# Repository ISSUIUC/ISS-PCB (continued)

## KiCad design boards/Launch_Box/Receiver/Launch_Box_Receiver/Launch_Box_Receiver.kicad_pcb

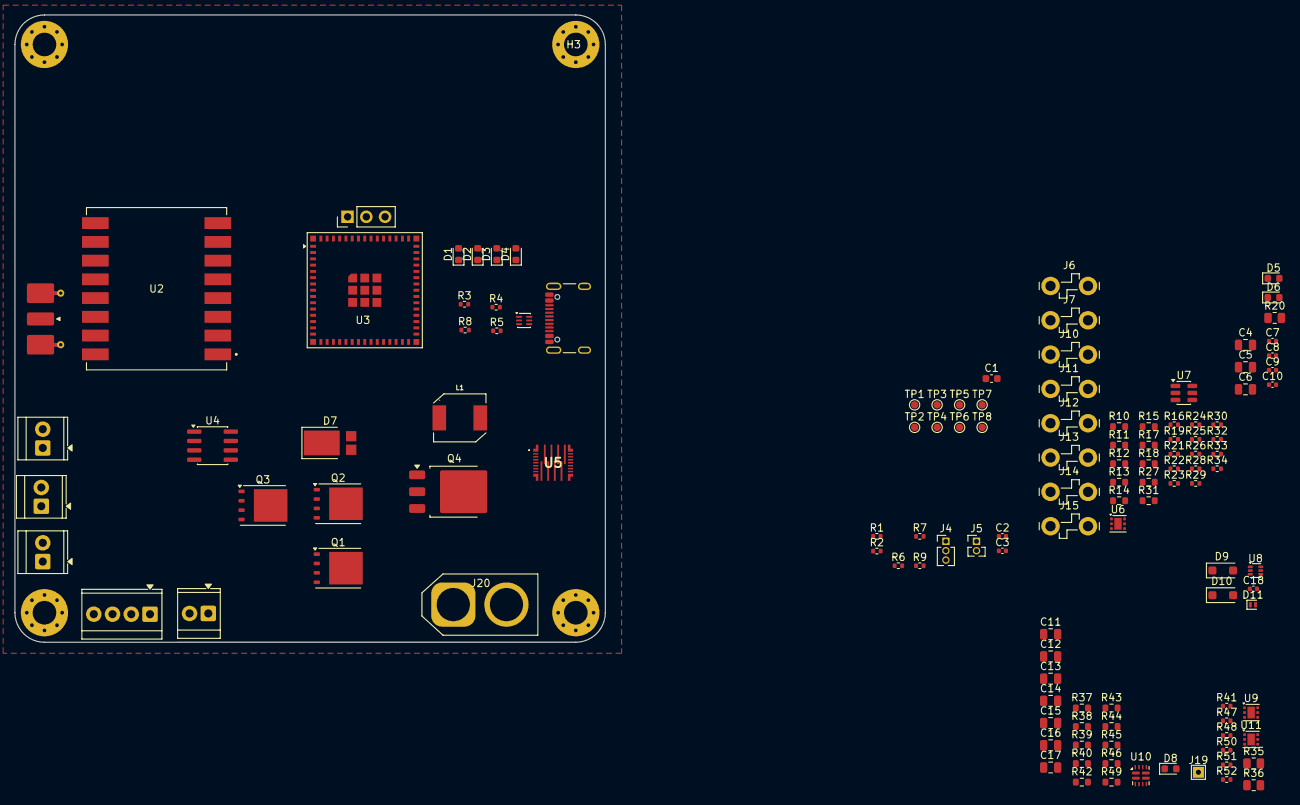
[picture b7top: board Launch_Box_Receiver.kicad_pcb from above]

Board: 4 copper layers, 80.0 x 85.0 mm, 129 parts (0 on the bottom side), 81 nets, no tracks yet.

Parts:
C1: 22uF; C_0603_1608Metric
C2: 100nF; C_0402_1005Metric
C3, C18: 1uF; C_0402_1005Metric
C4, C5: 4.7uF; C_0805_2012Metric
C6: 2.2uF; C_0805_2012Metric
C7, C8: 22pF; C_0402_1005Metric
C9: 1nF; C_0402_1005Metric
C10: 22nF; C_0402_1005Metric
C11: 0.1uF; C_0805_2012Metric
C12, C13: 10uF; C_0805_2012Metric
C14, C15, C16, C17: 22uF; C_0805_2012Metric
D1, D8: RED LED; LED_0603_1608Metric
D2: ORANGE LED; LED_0603_1608Metric
D3: GREEN LED; LED_0603_1608Metric
D4: BLUE LED; LED_0603_1608Metric
D5, D6: BLUE_LED; LED_0603_1608Metric
D7: SBR10U45SP5; D_PowerDI-5
D9: BZT52H-A5V1-QX; D_SOD-123F
D10: BZT52H-C15; D_SOD-123F
D11: BAS116L; D_SOD-882
H1, H2, H3, H4: M3; MountingHole_3.2mm_M3_Pad_Via
J1: USB4105-GF-A; USB_C_Receptacle_GCT_USB4105-xx-A_16P_TopMnt_Horizontal
J2: SMA; SMA_Molex_73251-2120_EdgeMount_Horizontal
J3: Conn_01x03; PinHeader_1x03_P2.54mm_Vertical
J4: Conn_01x03; PinHeader_1x03_P1.27mm_Vertical
J5: Conn_01x02; PinHeader_1x02_P1.27mm_Vertical
J6, J7, J10, J11, J12, J13, J14, J15: TE_1217861-1; TE_1217861-1_Faston_6.35mm_Vertical
J8: Screw_Terminal_01x04; TerminalBlock_TE_282834-4_1x04_P2.54mm_Horizontal
J9, J16, J17, J18: Screw_Terminal_01x02; TerminalBlock_TE_282834-2_1x02_P2.54mm_Horizontal
J19: TestPoint; TestPoint_THTPad_1.5x1.5mm_Drill0.7mm
J20: XT60 Male; AMASS_XT60-M_1x02_P7.20mm_Vertical
L1: 2.2uH; L_TDK_SPM6530
Q1, Q2, Q3: CSD17312Q5; TDSON-8-1
Q4: IPD068P03L3; TO-252-3_TabPin2
R1, R2: 5.1k; R_0402_1005Metric
R3, R4, R5, R8, R21, R22, R41: 470; R_0402_1005Metric
R6, R7: 4.7k; R_0402_1005Metric
R9: 20k; R_0402_1005Metric
R10, R11, R27, R38, R42: 200k; R_0603_1608Metric
R12, R14: 549; R_0603_1608Metric
R13, R15, R31, R46: 22k; R_0603_1608Metric
R16: 549; R_0402_1005Metric
R17, R18: 3.3k; R_0603_1608Metric
R19: 3.3k; R_0402_1005Metric
R20: 0R; R_0805_2012Metric
R23, R32: 100k; R_0402_1005Metric
R24, R25, R26: 10k; R_0402_1005Metric
R28: 10R; R_0402_1005Metric
R29, R30: 270R; R_0402_1005Metric
R33: 1.54k; R_0402_1005Metric
R34: 3.65k; R_0402_1005Metric
R35, R36: 2k; R_0805_2012Metric
R37: 470; R_0603_1608Metric
R39: 20k; R_0603_1608Metric
R40: 135k; R_0603_1608Metric
R43, R44: 30k; R_0603_1608Metric
R45: 26.1k; R_0603_1608Metric
R47: 62k; R_0402_1005Metric
R48: 16.9k; R_0402_1005Metric
R49: 100k; R_0603_1608Metric
R50: 21.5k; R_0402_1005Metric
R51, R52: 4.99k; R_0402_1005Metric
TP1, TP2, TP3, TP4, TP5, TP6, TP7, TP8: TestPoint_Small; TestPoint_Pad_D1.0mm
U1: ECMF02-2AMX6; ST_UQFN-6L_1.5x1.7mm_P0.5mm
U2: CORE1262-868M; XCVR_CORE1262-868M
U3: ESP32-S3-MINI-1U-N8; ESP32-S2-MINI-1U
U4: LM293; SOIC-8_3.9x4.9mm_P1.27mm
U5: TPS25990ARQPR; VQFN26_RQP_TEX
U6, U9, U11: TVS1400DRV; WSON-6-1EP_2x2mm_P0.65mm_EP1x1.6mm
U7: SRV05-4; SOT-23-6
U8: TI_TPS566242; SOT-563
U10: TPS2121; Texas_VQFN-HR-12_2x2.5mm_P0.5mm

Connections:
12V_VBAT: C5.1, D10.1 (K), Q4.3 (S), R20.1, R28.1, R47.1, U5.23 (VIN), U5.24 (VIN), U5.25 (VIN), U5.26 (VIN), U9.4 (IN), U9.5 (IN), U9.6 (IN), U10.7 (IN1)
+3V3: C1.1, C2.1, C14.1, C15.1, C16.1, C17.1, L1.1, R6.2, R7.2, R9.2, R23.1, R24.1, R25.1, R26.1, R37.1, R38.1, R40.2, R41.1, U2.8 (3V3), U3.3 (3V3), U4.8 (V+), U7.5 (VP)
/ALARM: R16.1, R19.1, U3.14 (IO10)
/ANT_SX1262: J2.1 (In), U2.16 (ANT)
/BOOT_SW: J3.1, U3.4 (IO0), U7.6 (IO4)
/CONTINUITY_1_LED: R21.1, R29.1, U3.12 (IO8), U7.1 (IO1)
/CONTINUITY_2_LED: R22.1, R30.1, U3.13 (IO9), U7.3 (IO2)
/D+: J1.A6 (D+), J1.B6 (D+), U1.6 (D+_out)
/D-: J1.A7 (D-), J1.B7 (D-), U1.5 (D-_out)
/FIRE_1: R12.2, R17.1, TP8.1 (1_1), U3.15 (IO11)
/FIRE_2: R14.2, R18.1, TP7.1 (1_1), U3.16 (IO12)
/I2C_SCL: J5.2, R7.1, U3.37 (IO41), U5.16 (SCL)
/I2C_SDA: J5.1, R6.1, U3.36 (IO40), U5.15 (SDA)
/IGN1_SENSE: R10.1, R13.1, U3.5 (IO1)
/IGN2_SENSE: R11.1, R15.1, U3.6 (IO2)
/LED_BLUE: R8.1, U3.19 (IO15)
/LED_GREEN: R5.1, U3.20 (IO16)
/LED_ORANGE: R4.1, U3.21 (IO17)
/LED_RED: R3.1, U3.22 (IO18)
/NFAULT: R26.2, U3.27 (IO47), U5.20 (GPIO2/FLT/COMP1/COMP2/EEDATA/EECLK)
/PG: R25.2, U3.25 (IO21), U5.19 (GPIO1/PGOOD/COMP1/COMP2/EEDATA/EECLK)
/Power/PMUX_GND: C18.1, D11.2 (A), R50.1, R51.2, R52.2, U10.3 (CP2), U10.6 (PR1), U10.9 (ST), U10.12 (GND)
/Power/VSYS: C11.1, C12.1, C13.1, J19.1 (Pin_1_1), R35.1, R39.1, R42.1, U8.1 (VIN), U10.1 (OUT), U10.8 (OUT)
/RESET_SW: C3.1, J3.2, R9.1, U3.45 (EN), U7.4 (IO3)
/SMBUS_ALERT: R24.2, U3.38 (IO42), U5.17 (GPIO4/SMBA/COMP1/COMP2/EEDATA/EECLK)
/SPI0_MISO: J4.3, U2.11 (MISO), U3.29 (IO34)
/SPI0_MOSI: J4.2, U2.12 (MOSI), U3.31 (IO35)
/SPI0_SCK: J4.1, U2.13 (CLK), U3.32 (IO36)
/SX1262_BUSY: U2.9 (BUSY), U3.26 (IO26)
/SX1262_CS: TP4.1 (1_1), U2.14 (CS), U3.40 (RXD0)
/SX1262_GPIO_1: U2.6 (DIO1), U3.18 (IO14)
/SX1262_GPIO_2: U2.5 (DIO2), U3.17 (IO13)
/SX1262_RESET: U2.10 (RESET), U3.28 (IO33)
/SX1262_RX_EN: TP6.1 (1_1), U2.3 (RXEN), U3.34 (IO38)
/SX1262_TX_EN: TP5.1 (1_1), U2.4 (TXEN), U3.33 (IO37)
/USB_D+: U1.1 (D+_in), U3.24 (USB_D+)
/USB_D-: U1.2 (D-_in), U3.23 (USB_D-)
/USB_POWER: J1.A4 (VBUS), J1.A9 (VBUS), J1.B4 (VBUS), J1.B9 (VBUS), R48.1, U10.2 (IN2), U11.4 (IN), U11.5 (IN), U11.6 (IN)
/User Interface/ALARM-: J9.2, Q3.5 (D)
/User Interface/Igniter_1-: J12.1 (1_1), Q1.5 (D), R10.2
/User Interface/Igniter_2-: J13.1 (1_1), Q2.5 (D), R11.2
/VBAT_ENABLE: R32.1, U3.30 (IO48), U5.18 (EN/UVLO)
/VPRYO_SENSE: R27.2, R31.1, U3.10 (IO6)
GND: C1.2, C2.2, C3.2, C4.2, C5.2, C6.2, C7.2, C8.2, C9.2, C10.2, C11.2, C12.2, C13.2, C14.2, C15.2, C16.2, C17.2, D1.1 (K), D2.1 (K), D3.1 (K), D4.1 (K), D5.1 (K), D6.1 (K), D7.2 (A), D8.1 (K), D9.2 (A), D11.1 (K), J1.A1 (GND), J1.A12 (GND), J1.B1 (GND), J1.B12 (GND), J1.S1 (SHIELD), J2.2 (Ext), J3.3, J8.2, J8.4, J14.1 (1_1), J15.1 (1_1), J16.2, J17.2, J18.2, J20.1, Q1.1 (S), Q1.2 (S), Q1.3 (S), Q2.1 (S), Q2.2 (S), Q2.3 (S), Q3.1 (S), Q3.2 (S), Q3.3 (S), R1.2, R2.2, R13.2, R15.2, R17.2, R18.2, R19.2, R31.2, R32.2, R33.2, R34.2, R43.2, R44.2, R45.2, R46.2, R49.2, U1.3 (GND), U2.1 (GND), U2.2 (GND), U2.7 (GND), U2.15 (GND), U3.1 (GND), U3.2 (GND), U3.42 (GND), U3.43 (GND), U3.46 (GND), U3.47 (GND), U3.48 (GND), U3.49 (GND), U3.50 (GND), U3.51 (GND), U3.52 (GND), U3.53 (GND), U3.54 (GND), U3.55 (GND), U3.56 (GND), U3.57 (GND), U3.58 (GND), U3.59 (GND), U3.60 (GND), U3.61 (GND), U3.62 (GND), U3.63 (GND), U3.64 (GND), U3.65 (GND), U4.4 (V-), U5.14 (GND), U6.1 (GND), U6.2 (GND), U6.3 (GND), U6.7 (GND), U7.2 (VN), U8.3 (GND), U8.4 (AGND), U9.1 (GND), U9.2 (GND), U9.3 (GND), U9.7 (GND), U11.1 (GND), U11.2 (GND), U11.3 (GND), U11.7 (GND)
unnamed: D1.2 (A), R3.2
unnamed: D2.2 (A), R4.2
unnamed: D3.2 (A), R5.2
unnamed: D4.2 (A), R8.2
unnamed: D5.2 (A), R21.2
unnamed: D6.2 (A), R22.2
unnamed: C4.1, D7.1 (K), J6.1 (1_1), R20.2, U5.10 (VOUT), U5.11 (VOUT), U5.12 (VOUT), U5.13 (VOUT)
unnamed: D8.2 (A), R41.2
unnamed: D9.1 (K), R39.2, R44.1, U8.5 (EN)
unnamed: D10.2 (A), Q4.1 (G), R49.1
unnamed: J1.A5 (CC1), R1.1
unnamed: J1.B5 (CC2), R2.1
unnamed: J8.1, R29.2
unnamed: J8.3, R30.2
unnamed: J16.1, R37.2
unnamed: J17.1, R35.2
unnamed: J18.1, R36.2
unnamed: J20.2, Q4.2 (D)
unnamed: Q1.4 (G), R12.1, U4.1
unnamed: Q2.4 (G), R14.1, U4.7
unnamed: Q3.4 (G), R16.2
unnamed: C10.1, U5.4 (DVDT)
unnamed: R23.2, U5.21 (GPIO3/SWEN/COMP1/COMP2/EEDATA/EECLK)
unnamed: R33.1, U5.8 (ILIM)
unnamed: C8.1, R34.1, U5.7 (IMON)
unnamed: C9.1, U5.9 (IREF/DAC2)
unnamed: C7.1, U5.5 (TEMP/CMP)
unnamed: C6.1, R28.2, U5.22 (VDD)
unnamed: R40.1, R43.1, U8.6 (FB)
unnamed: L1.2, U8.2 (SW)
unnamed: R50.2, U10.10 (ILM)
unnamed: R47.2, R51.1, U10.5 (OV1)
unnamed: R48.2, R52.1, U10.4 (OV2)
unnamed: C18.2, U10.11 (SS)
V_IGN: J7.1 (1_1), J9.1, J10.1 (1_1), J11.1 (1_1), R27.1, R36.1, U6.4 (IN), U6.5 (IN), U6.6 (IN)
cmp_in_reg_rail: R42.2, R46.1, TP2.1 (1_1), U3.8 (IO4), U4.3 (+), U4.5 (+)
cmp_out_reg_rail: R38.2, R45.1, TP1.1 (1_1), U3.9 (IO5), U4.2 (-), U4.6 (-)

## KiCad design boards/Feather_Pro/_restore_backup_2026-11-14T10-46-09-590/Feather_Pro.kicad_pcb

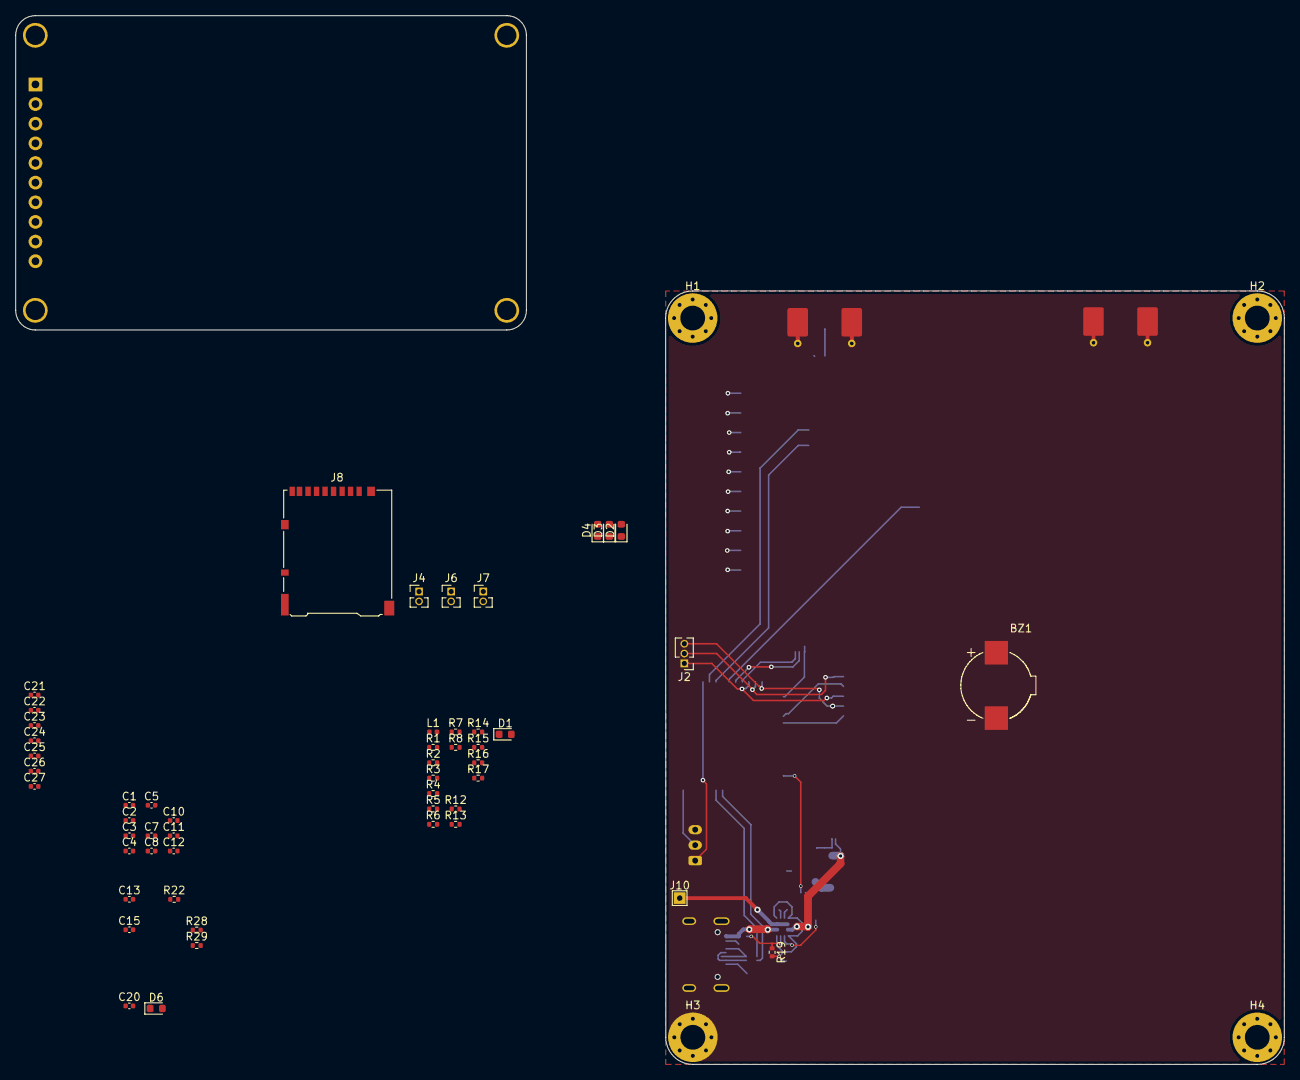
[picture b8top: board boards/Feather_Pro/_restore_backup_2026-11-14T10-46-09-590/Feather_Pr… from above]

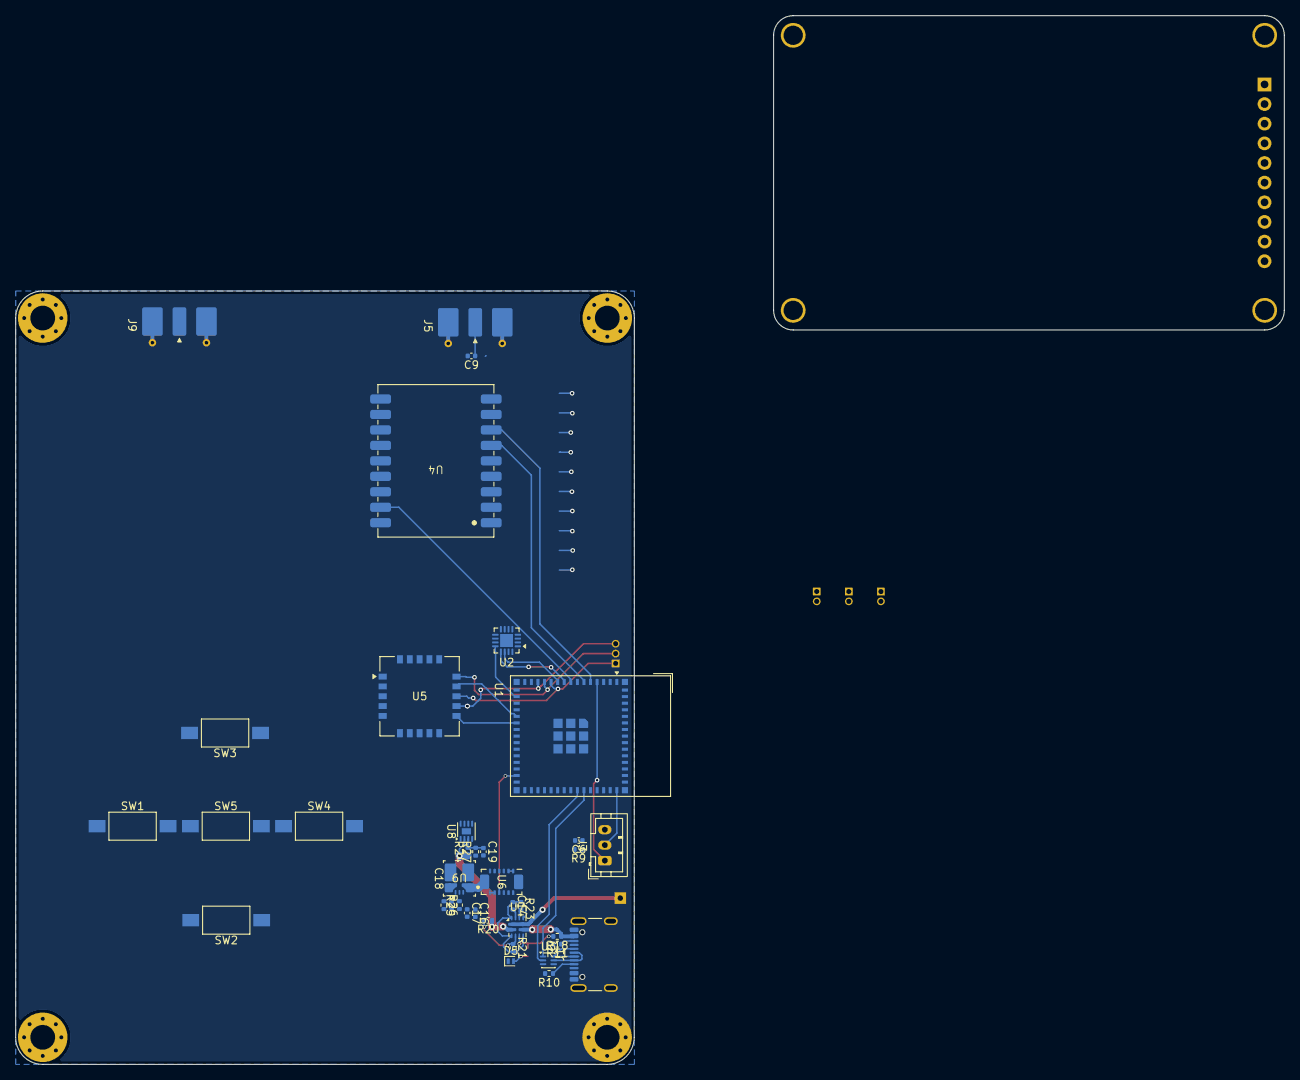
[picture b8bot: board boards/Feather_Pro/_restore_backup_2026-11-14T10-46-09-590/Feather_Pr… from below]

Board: 4 copper layers, 164.0 x 135.6 mm, 93 parts (37 on the bottom side), 76 nets.

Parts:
BZ1: Buzzer; Buzzer_SMTB-0927-TW-R
C1, C4, C5, C6, C7, C14, C26: 1uF; C_0402_1005Metric
C2, C20: 22uF; C_0402_1005Metric
C3, C13, C21, C22, C23, C24, C25: 0.1uF; C_0402_1005Metric
C8, C10, C17, C27: 100nF; C_0402_1005Metric
C9: 100pF; C_0402_1005Metric
C11: 10uF; C_0402_1005Metric
C12, C18: 10nF; C_0402_1005Metric
C15: 0.1 uF; C_0402_1005Metric
C16: 10Uf; C_0402_1005Metric
C19: 1 uF; C_0402_1005Metric
D1: RED LED; LED_0603_1608Metric
D2: ORANGE LED; LED_0603_1608Metric
D3: GREEN LED; LED_0603_1608Metric
D4: BLUE LED; LED_0603_1608Metric
D5: BAS116L; D_SOD-882
D6: LED; LED_0603_1608Metric
H1, H2, H3, H4: M3; MountingHole_3.2mm_M3_Pad_Via
J1: USB4105-GF-A; USB_C_Receptacle_GCT_USB4105-xx-A_16P_TopMnt_Horizontal
J2: Conn_01x03; PinHeader_1x03_P1.27mm_Vertical
J3: Conn_01x03; JST_PH_B3B-PH-K_1x03_P2.00mm_Vertical
J4, J6, J7: Conn_01x02; PinHeader_1x02_P1.27mm_Vertical
J5, J9: SMA; SMA_Molex_73251-2120_EdgeMount_Horizontal
J8: DM3AT-SF-PEJM5; microSD_HC_Hirose_DM3AT-SF-PEJM5
J10: TestPoint; TestPoint_THTPad_1.5x1.5mm_Drill0.7mm
L1: 330nH; L_0402_1005Metric
R1, R24, R27: 0; R_0402_1005Metric
R2, R17: 100k; R_0402_1005Metric
R3, R4, R5, R6, R29: 470; R_0402_1005Metric
R7, R8: 4.7k; R_0402_1005Metric
R9: 20k; R_0402_1005Metric
R10, R11: 5.1k; R_0402_1005Metric
R12, R13, R14, R15, R16, R22, R26: 10k; R_0402_1005Metric
R18, R20: 16.9k; R_0402_1005Metric
R19, R21: 5k; R_0402_1005Metric
R23: 21.5k; R_0402_1005Metric
R25: 11.8k; R_0402_1005Metric
R28: 10K; R_0402_1005Metric
SW1, SW2, SW3, SW4, SW5: SW_Push; SW_SPST_FSMSM
U1: ESP32-S3-MINI-1; ESP32-S2-MINI-1
U2: ADS7138-Q1; WQFN-16-1EP_3x3mm_P0.5mm_EP1.68x1.68mm
U3: ECMF02-2AMX6; ST_UQFN-6L_1.5x1.7mm_P0.5mm
U4: LR2021
U5: E22-400MM22S
U6: INA745x; VQFN-REL0014B
U7: TPS2121; Texas_VQFN-HR-12_2x2.5mm_P0.5mm
U8: MAX17048G+T10; TDFN-8-1EP_2x2mm_P0.5mm_EP0.8x1.2mm
U9: TPSM863253RDXR; QFN-FCMOD-RDX0007A
U10: LCD_2.2_in; Adafruit_2.2_LCD_SCREEN

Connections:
+3V3: C2.1, C3.1, C4.1, C5.1, C7.1, C8.1, C11.1, C12.1, C13.2, C20.1, C26.1, C27.1, J8.4 (VDD), R7.2, R8.2, R9.2, R12.2, R13.2, R14.2, R15.2, R16.2, R17.2, R22.1, R27.1, R28.1, R29.1, U1.3 (3V3), U2.7 (AVDD), U2.10 (DVDD), U4.1 (VCC), U5.1 (VCC), U6.3 (A1), U6.11 (VS), U9.3 (VOUT), U9.7 (FB), U10.9 (VIN)
/ADS_ALERT: U1.17 (IO13), U2.12 (ALERT)
/BOOT_SW: J3.1, U1.4 (IO0)
/BUTTON_CENTER: C25.2, SW5.2, U1.30 (IO48)
/BUTTON_DOWN: C22.1, SW2.1, U1.35 (IO39)
/BUTTON_LEFT: C24.2, SW4.2, U1.34 (IO38)
/BUTTON_RIGHT: C21.1, SW1.1, U1.31 (IO35)
/BUTTON_UP: C23.1, SW3.1, U1.32 (IO36)
/BUZZER: BZ1.1 (+), U2.15 (AIN0/GPIO0)
/D+: J1.A6 (D+), J1.B6 (D+), U3.6 (D+_out)
/D-: J1.A7 (D-), J1.B7 (D-), U3.5 (D-_out)
/E22_BUSY: U1.21 (IO17), U5.11 (BUSY)
/E22_CS: U1.20 (IO16), U5.14 (NSS)
/E22_DIO1: U1.18 (IO14), U5.20 (DIO1)
/E22_DIO3: U1.19 (IO15), U5.18 (DIO3)
/E22_RESET: C10.1, R17.1, U1.23 (USB_D-), U5.3 (NRST)
/E22_RXEN: U1.22 (IO18), U5.10 (RXEN)
/Feather_Pro_Power/PMUX_GND: C14.1, D5.2 (A), R19.2, R21.2, R23.1, U7.3 (CP2), U7.6 (PR1), U7.9 (ST), U7.12 (GND)
/GPIO_0: J7.1, U2.5 (AIN6/GPIO6)
/GPIO_1: J7.2, U2.6 (AIN7/GPIO7)
/I2C_SCL: J4.2, R8.1, U1.9 (IO5), U2.13 (SCL), U6.6 (SCL), U8.7 (SCL)
/I2C_SDA: J4.1, R7.1, U1.10 (IO6), U2.14 (SDA), U6.5 (SDA), U8.8 (SDA)
/INA_ALERT: R22.2, U1.29 (IO34), U6.10 (ALERT)
/LCD_BL: U1.25 (IO21), U10.1 (BL)
/LCD_CS: U1.28 (IO33), U10.5 (CS)
/LCD_D_C: U1.24 (USB_D+), U10.8 (D/C)
/LCD_RST: U1.27 (IO47), U10.7 (RST)
/LED_BLUE: R6.1, U2.3 (AIN4/GPIO4)
/LED_GREEN: R5.1, U2.2 (AIN3/GPIO3)
/LED_ORANGE: R4.1, U2.1 (ANI2/GPIO2)
/LED_RED: R3.1, U2.16 (AIN1/GPIO1)
/LR2021_ANT: C9.2, U4.9 (ANT)
/LR2021_BUSY: U1.5 (IO1), U4.7 (BUSY)
/LR2021_CS: U1.6 (IO2), U4.6 (~CS)
/LR2021_GPIO7: U1.8 (IO4), U4.17 (DIO7)
/LR2021_GPIO8: U1.14 (IO10), U4.16 (DIO8)
/LR2021_GPIO9: U1.15 (IO11), U4.15 (DIO9)
/LR2021_nRST: U1.16 (IO12), U4.14 (nRST)
/MAX_ALERT: R28.2, U2.4 (AIN5/GPIO5), U8.5 (*ALRT)
/MicroSD_CLK: J8.5 (CLK), U1.36 (IO40)
/MicroSD_CMD: J8.3 (CMD), R14.1, U1.38 (IO42)
/MicroSD_DAT0: J8.7 (DAT0), R13.1, U1.37 (IO41)
/RESET_SW: C6.1, J3.2, R9.1, U1.45 (EN)
/SPI_MISO: J2.3, U1.13 (IO9), U4.3 (MISO), U5.12 (MISO), U10.3 (MISO)
/SPI_MOSI: J2.1, U1.11 (IO7), U4.4 (MOSI), U5.13 (MOSI), U10.4 (MOSI)
/SPI_SCK: J2.2, U1.12 (IO8), U4.5 (SCK), U5.15 (SCK), U10.2 (SCK)
/SYS_POWER: J10.1 (Pin_1_1), U6.13 (VBUS), U6.14 (IS+), U7.1 (OUT), U7.8 (OUT)
/USB_D+: U1.40 (RXD0), U3.1 (D+_in)
/USB_D-: U1.39 (TXD0), U3.2 (D-_in)
/USB_POWER: J1.A4 (VBUS), J1.A9 (VBUS), J1.B4 (VBUS), J1.B9 (VBUS), R18.1, U7.7 (IN1)
/VBAT: C15.1, J6.1, R20.1, R24.1, U7.2 (IN2), U8.2 (CELL)
/VREG_IN: C16.1, C17.1, R25.1, U6.7 (IS-), U9.1 (VIN)
GND: BZ1.2 (-), C1.2, C2.2, C3.2, C4.2, C5.2, C6.2, C7.2, C8.2, C10.2, C11.2, C12.2, C13.1, C15.2, C16.2, C17.2, C18.2, C19.2, C20.2, C21.2, C22.2, C23.2, C24.1, C25.1, C26.2, C27.2, D1.1 (K), D2.1 (K), D3.1 (K), D4.1 (K), D5.1 (K), D6.1 (K), J1.A1 (GND), J1.A12 (GND), J1.B1 (GND), J1.B12 (GND), J3.3, J5.2 (Ext), J6.2, J8.6 (VSS), J9.2 (Ext), L1.2, R1.1, R10.2, R11.2, R26.2, SW1.2, SW2.2, SW3.2, SW4.1, SW5.1, U1.1 (GND), U1.2 (GND), U1.42 (GND), U1.43 (GND), U1.46 (GND), U1.47 (GND), U1.48 (GND), U1.49 (GND), U1.50 (GND), U1.51 (GND), U1.52 (GND), U1.53 (GND), U1.54 (GND), U1.55 (GND), U1.56 (GND), U1.57 (GND), U1.58 (GND), U1.59 (GND), U1.60 (GND), U1.61 (GND), U1.62 (GND), U1.63 (GND), U1.64 (GND), U1.65 (GND), U2.9 (GND), U2.17 (EPAD), U3.3 (GND), U4.2 (GND), U4.8 (GND), U4.11 (GND), U4.12 (GND), U4.18 (GND), U5.2 (GND), U5.7 (GND), U5.16 (GND), U6.4 (A0), U6.12 (GND), U8.1 (CTG), U8.4 (GND), U8.6 (QSTRT), U8.9 (EPAD), U9.4 (PGND), U10.10 (GND)
unnamed: D1.2 (A), R3.2
unnamed: D2.2 (A), R4.2
unnamed: D3.2 (A), R5.2
unnamed: D4.2 (A), R6.2
unnamed: D6.2 (A), R29.2
unnamed: J1.A5 (CC1), R10.1
unnamed: J1.B5 (CC2), R11.1
unnamed: C9.1, J5.1 (In)
unnamed: J8.8 (DAT1), R12.1
unnamed: J8.1 (DAT2), R16.1
unnamed: J8.2 (DAT3/CD), R15.1
unnamed: J9.1 (In), L1.1, U5.6 (ANT)
unnamed: R1.2, R2.2, U2.11 (ADDR)
unnamed: C1.1, R2.1, U2.8 (DECAP)
unnamed: U5.9 (TXEN), U5.19 (DIO2)
unnamed: U6.1 (SH+), U6.2 (IN+)
unnamed: U6.8 (SH-), U6.9 (IN-)
unnamed: R23.2, U7.10 (ILM)
unnamed: R18.2, R19.1, U7.5 (OV1)
unnamed: R20.2, R21.1, U7.4 (OV2)
unnamed: C14.2, U7.11 (SS)
unnamed: C19.1, R24.2, R27.2, U8.3 (VDD)
unnamed: C18.1, R25.2, R26.1, U9.6 (EN)

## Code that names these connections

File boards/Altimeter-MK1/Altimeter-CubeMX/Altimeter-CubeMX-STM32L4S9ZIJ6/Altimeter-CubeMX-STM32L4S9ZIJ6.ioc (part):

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Mcu.Name=STM32L4S9ZIJx
Mcu.Package=UFBGA144
Mcu.UserName=STM32L4S9ZIJx
PA0.GPIOParameters=GPIO_Label
PA0.GPIO_Label=sense_e
PA0.Signal=ADCx_IN5
PA1.GPIOParameters=GPIO_Label
PA1.GPIO_Label=sense_f
PA1.Signal=ADCx_IN6
PA10.GPIOParameters=GPIO_Label
PA10.GPIO_Label=TELEM_CS
PA10.Signal=GPIO_Output
PA11.GPIOParameters=GPIO_Label
PA11.GPIO_Label=USB_DM
PA11.Mode=Device_Only
PA11.Signal=USB_OTG_FS_DM
PA12.GPIOParameters=GPIO_Label
PA12.GPIO_Label=USB_DP
PA12.Mode=Device_Only
PA12.Signal=USB_OTG_FS_DP
PA13\ (JTMS/SWDIO).GPIOParameters=GPIO_Label
PA13\ (JTMS/SWDIO).GPIO_Label=SWDIO
PA13\ (JTMS/SWDIO).Mode=Trace_Asynchronous_SW
PA13\ (JTMS/SWDIO).Signal=SYS_JTMS-SWDIO
PA14\ (JTCK/SWCLK).GPIOParameters=GPIO_Label
PA14\ (JTCK/SWCLK).GPIO_Label=SWSCLK
PA14\ (JTCK/SWCLK).Mode=Trace_Asynchronous_SW
PA14\ (JTCK/SWCLK).Signal=SYS_JTCK-SWCLK
PA15\ (JTDI).GPIOParameters=GPIO_Label
PA15\ (JTDI).GPIO_Label=RESERVED_JTDI
PA15\ (JTDI).Signal=SYS_JTDI
PA2.GPIOParameters=GPIO_Label
PA2.GPIO_Label=sense_vFlight
PA2.Signal=ADCx_IN7
PA3.GPIOParameters=GPIO_Label
PA3.GPIO_Label=sense_vPyro
PA3.Signal=ADCx_IN8
PA8.GPIOParameters=GPIO_Label
PA8.GPIO_Label=RESERVED_TIM1_CH1_PWM
PA8.Signal=S_TIM1_CH1
PA9.GPIOParameters=GPIO_Label
PA9.GPIO_Label=RESERVED_TIM1_CH2_PWM
PA9.Signal=S_TIM1_CH2
PB10.GPIOParameters=GPIO_Label
PB10.GPIO_Label=TELEM_SCK
PB10.Mode=Full_Duplex_Master
PB10.Signal=SPI2_SCK
PB15.GPIOParameters=GPIO_Label
PB15.GPIO_Label=TELEM_MOSI
PB15.Mode=Full_Duplex_Master
PB15.Signal=SPI2_MOSI
PB2.GPIOParameters=GPIO_Label
PB2.GPIO_Label=BUZZER_PWM
PB2.Mode=WaveformGeneration
PB2.Signal=LPTIM1_OUT
PB3\ (JTDO/TRACESWO).GPIOParameters=GPIO_Label
PB3\ (JTDO/TRACESWO).GPIO_Label=SWO
PB3\ (JTDO/TRACESWO).Mode=Trace_Asynchronous_SW
PB3\ (JTDO/TRACESWO).Signal=SYS_JTDO-SWO
PB4\ (NJTRST).GPIOParameters=GPIO_Label
PB4\ (NJTRST).GPIO_Label=RESERVED_PB4
PB4\ (NJTRST).Signal=SYS_JTRST
PB5.GPIOParameters=GPIO_Label
PB5.GPIO_Label=RESERVED_TIM3_CH2_PWM
PB5.Signal=S_TIM3_CH2
PB6.GPIOParameters=GPIO_Label
PB6.GPIO_Label=RESERVED_USART1_TX
PB6.Mode=Multiprocessor_communication
PB6.Signal=USART1_TX
PB7.GPIOParameters=GPIO_Label
PB7.GPIO_Label=RESERVED_USART1_RX
PB7.Mode=Multiprocessor_communication
PB7.Signal=USART1_RX
PB8.GPIOParameters=GPIO_Label
PB8.GPIO_Label=LED_BLUE
PB8.Signal=GPIO_Output
PB9.GPIOParameters=GPIO_Label
PB9.GPIO_Label=LED_ORANGE
PB9.Signal=GPIO_Output
PC0.GPIOParameters=GPIO_Label
PC0.GPIO_Label=sense_a
PC0.Signal=ADCx_IN1
PC1.GPIOParameters=GPIO_Label
PC1.GPIO_Label=sense_b
PC1.Signal=ADCx_IN2
PC10.GPIOParameters=GPIO_Label
PC10.GPIO_Label=RESERVED_SDMMC1_D2
PC10.Mode=SD_4_bits_Wide_bus
PC10.Signal=SDMMC1_D2
PC11.GPIOParameters=GPIO_Label
PC11.GPIO_Label=RESERVED_SDMMC1_D3
PC11.Mode=SD_4_bits_Wide_bus
PC11.Signal=SDMMC1_D3
PC12.GPIOParameters=GPIO_Label
PC12.GPIO_Label=RESERVED_SDMMC1_CK
PC12.Mode=SD_4_bits_Wide_bus
PC12.Signal=SDMMC1_CK
PC13.GPIOParameters=GPIO_Label
PC13.GPIO_Label=LSM9DS1_INT2_A/G
PC13.Signal=GPIO_Input
PC14-OSC32_IN\ (PC14).GPIOParameters=GPIO_Label
PC14-OSC32_IN\ (PC14).GPIO_Label=TELEM_GPIO_5
PC14-OSC32_IN\ (PC14).Signal=GPIO_Input
PC15-OSC32_OUT\ (PC15).GPIOParameters=GPIO_Label
PC15-OSC32_OUT\ (PC15).GPIO_Label=TELEM_GPIO_4
PC15-OSC32_OUT\ (PC15).Signal=GPIO_Input
PC2.GPIOParameters=GPIO_Label
PC2.GPIO_Label=sense_c
PC2.Signal=ADCx_IN3
PC3.GPIOParameters=GPIO_Label
PC3.GPIO_Label=sense_d
PC3.Signal=ADCx_IN4
PC6.GPIOParameters=GPIO_Label,GPIO_Mode
PC6.GPIO_Label=TELEM_INT
PC6.GPIO_Mode=GPIO_MODE_INPUT
PC6.Signal=GPIO_Input
PC7.GPIOParameters=GPIO_Label,GPIO_Mode
PC7.GPIO_Label=SAM-M8Q_EXTINT
PC7.GPIO_Mode=GPIO_MODE_INPUT
PC7.Signal=GPIO_Input
PC8.GPIOParameters=GPIO_Label
PC8.GPIO_Label=RESERVED_SDMMC1_D0
PC8.Mode=SD_4_bits_Wide_bus
PC8.Signal=SDMMC1_D0
PC9.GPIOParameters=GPIO_Label
PC9.GPIO_Label=RESERVED_SDMMC1_D1
PC9.Mode=SD_4_bits_Wide_bus
PC9.Signal=SDMMC1_D1
PD0.GPIOParameters=GPIO_Label
PD0.GPIO_Label=FMC_D2
PD0.Signal=FMC_D2_DA2
PD1.GPIOParameters=GPIO_Label
PD1.GPIO_Label=FMC_D3
PD1.Signal=FMC_D3_DA3
PD11.GPIOParameters=GPIO_Label
PD11.GPIO_Label=FMC_CLE
PD11.Signal=FMC_A16_CLE
PD12.GPIOParameters=GPIO_Label
PD12.GPIO_Label=FMC_ALE
PD12.Signal=FMC_A17_ALE
PD14.GPIOParameters=GPIO_Label
PD14.GPIO_Label=FMC_D0
PD14.Signal=FMC_D0_DA0
PD15.GPIOParameters=GPIO_Label
PD15.GPIO_Label=FMC_D1
PD15.Signal=FMC_D1_DA1
PD2.GPIOParameters=GPIO_Label
PD2.GPIO_Label=RESERVED_SDMMC1_CMD
PD2.Mode=SD_4_bits_Wide_bus
PD2.Signal=SDMMC1_CMD
PD3.GPIOParameters=GPIO_Label
PD3.GPIO_Label=TELEM_MISO
PD3.Mode=Full_Duplex_Master
PD3.Signal=SPI2_MISO
PD4.GPIOParameters=GPIO_Label
PD4.GPIO_Label=FMC_RE
PD4.Signal=FMC_NOE
PD5.GPIOParameters=GPIO_Label
PD5.GPIO_Label=FLASH_WE
PD5.Signal=FMC_NWE
PD6.GPIOParameters=GPIO_Label
PD6.GPIO_Label=FMC_NWAIT
PD6.Signal=FMC_NWAIT
PD7.GPIOParameters=GPIO_Label
PD7.GPIO_Label=FMC_CE
PD7.Mode=NandChipSelect3_1
PD7.Signal=FMC_NCE
PE0.GPIOParameters=GPIO_Label
PE0.GPIO_Label=LED_RED
PE0.Signal=GPIO_Output
PE1.GPIOParameters=GPIO_Label
PE1.GPIO_Label=H3LIS331DL_CS
PE1.Signal=GPIO_Output
PE10.GPIOParameters=GPIO_Label
PE10.GPIO_Label=FMC_D7
PE10.Signal=FMC_D7_DA7
PE2.GPIOParameters=GPIO_Label
PE2.GPIO_Label=MS5611_CS
PE2.Signal=GPIO_Output
PE3.GPIOParameters=GPIO_Label
PE3.GPIO_Label=RESERVED_TIM3_CH1_PWM
PE3.Signal=S_TIM3_CH1
PE4.GPIOParameters=GPIO_Label
PE4.GPIO_Label=TELEM_GPIO_3
PE4.Signal=GPIO_Input
PE5.GPIOParameters=GPIO_Label
PE5.GPIO_Label=LSM9DS1_CS_M
PE5.Signal=GPIO_Output
PE6.GPIOParameters=GPIO_Label
PE6.GPIO_Label=TELEM_GPIO_2
PE6.Signal=GPIO_Input
PE7.GPIOParameters=GPIO_Label
PE7.GPIO_Label=FMC_D4
PE7.Signal=FMC_D4_DA4
PE8.GPIOParameters=GPIO_Label
PE8.GPIO_Label=FMC_D5
PE8.Signal=FMC_D5_DA5
PE9.GPIOParameters=GPIO_Label
PE9.GPIO_Label=FMC_D6
PE9.Signal=FMC_D6_DA6
PF0.GPIOParameters=GPIO_Label
PF0.GPIO_Label=SAM-M8Q_SDA
PF0.Mode=I2C
PF0.Signal=I2C2_SDA
PF1.GPIOParameters=GPIO_Label
PF1.GPIO_Label=SAM-M8Q_SCL
PF1.Mode=I2C
PF1.Signal=I2C2_SCL
PF2.GPIOParameters=GPIO_Label
PF2.GPIO_Label=LSM9DS1_INT1_A/G
PF2.Signal=GPIO_Input
PF3.GPIOParameters=GPIO_Label
PF3.GPIO_Label=LSM9DS1_INT1_M
PF3.Signal=GPIO_Input
PF4.GPIOParameters=GPIO_Label
PF4.GPIO_Label=TELEM_RST
PF4.Signal=GPIO_Input
PF5.GPIOParameters=GPIO_Label
PF5.GPIO_Label=LED_GREEN
PF5.Signal=GPIO_Output
PF6.GPIOParameters=GPIO_Label
PF6.GPIO_Label=MCU_TPS2594_GP
PF6.Signal=GPIO_Input
PF8.GPIOParameters=GPIO_Label
PF8.GPIO_Label=LSM9DS1_DEN_A/G
PF8.Signal=GPIO_Input
PG10.GPIOParameters=GPIO_Label
PG10.GPIO_Label=H3LIS331DL_INT1
PG10.Signal=GPIO_Input
PG12.GPIOParameters=GPIO_Label
PG12.GPIO_Label=TELEM_GPIO_1
PG12.Signal=GPIO_Input
PG13.GPIOParameters=GPIO_Label
PG13.GPIO_Label=LSM9DS1_CS_A/G
PG13.Signal=GPIO_Output
PG2.GPIOParameters=GPIO_Label
PG2.GPIO_Label=SNS_SCK
PG2.Mode=Full_Duplex_Master
PG2.Signal=SPI1_SCK
PG3.GPIOParameters=GPIO_Label
PG3.GPIO_Label=SNS_MISO
PG3.Mode=Full_Duplex_Master
PG3.Signal=SPI1_MISO
PG4.GPIOParameters=GPIO_Label
PG4.GPIO_Label=SNS_MOSI
PG4.Mode=Full_Duplex_Master
PG4.Signal=SPI1_MOSI
PG7.GPIOParameters=GPIO_Label
PG7.GPIO_Label=LSM9DS1_DRDY_M
PG7.Signal=GPIO_Input
PG8.GPIOParameters=GPIO_Label
PG8.GPIO_Label=H3LIS331DL_INT2
PG8.Signal=GPIO_Input
PH0-OSC_IN\ (PH0).GPIOParameters=GPIO_Label
PH0-OSC_IN\ (PH0).GPIO_Label=HSE_CLK
PH0-OSC_IN\ (PH0).Mode=HSE-External-Clock-Source
PH0-OSC_IN\ (PH0).Signal=RCC_OSC_IN
RCC.HSE_VALUE=8000000
RCC.SYSCLKFreq_VALUE=120000000
RCC.SYSCLKSource=RCC_SYSCLKSOURCE_PLLCLK
board=custom

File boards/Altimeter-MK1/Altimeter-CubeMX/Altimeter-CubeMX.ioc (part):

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Mcu.Name=STM32U585QIIx
Mcu.Package=UFBGA132
Mcu.UserName=STM32U585QIIx
PA0.GPIOParameters=GPIO_Label
PA0.GPIO_Label=RESERVED_TIM5_CH1_PWM
PA0.Signal=S_TIM5_CH1
PA1.GPIOParameters=GPIO_Label
PA1.GPIO_Label=SNS_SCK
PA1.Mode=Full_Duplex_Master
PA1.Signal=SPI1_SCK
PA11.GPIOParameters=GPIO_Label
PA11.GPIO_Label=USB_DM
PA11.Mode=Device_Only
PA11.Signal=USB_OTG_FS_DM
PA12.GPIOParameters=GPIO_Label
PA12.GPIO_Label=USB_DP
PA12.Mode=Device_Only
PA12.Signal=USB_OTG_FS_DP
PA13\ (JTMS/SWDIO).GPIOParameters=GPIO_Label
PA13\ (JTMS/SWDIO).GPIO_Label=SWDIO
PA13\ (JTMS/SWDIO).Mode=Trace_Asynchronous_SW
PA13\ (JTMS/SWDIO).Signal=DEBUG_JTMS-SWDIO
PA14\ (JTCK/SWCLK).GPIOParameters=GPIO_Label
PA14\ (JTCK/SWCLK).GPIO_Label=SWCLK
PA14\ (JTCK/SWCLK).Mode=Trace_Asynchronous_SW
PA14\ (JTCK/SWCLK).Signal=DEBUG_JTCK-SWCLK
PA15\ (JTDI).GPIOParameters=GPIO_Label
PA15\ (JTDI).GPIO_Label=RESERVED_CC1/JTDI
PA15\ (JTDI).Mode=Sink_AllSignals
PA15\ (JTDI).Signal=UCPD1_CC1
PA4.GPIOParameters=GPIO_Label
PA4.GPIO_Label=MCU_TPS2594_GP
PA4.Signal=GPIO_Input
PA7.GPIOParameters=GPIO_Label
PA7.GPIO_Label=LSM9DS1_DRDY_M
PA7.Signal=GPIO_Input
PA8.GPIOParameters=GPIO_Label
PA8.GPIO_Label=LSM9DS1_DEN_A/G
PA8.Signal=GPIO_Input
PB15.GPIOParameters=GPIO_Label
PB15.GPIO_Label=RESERVED_CC2
PB15.Mode=Sink_AllSignals
PB15.Signal=UCPD1_CC2
PB3\ (JTDO/TRACESWO).GPIOParameters=GPIO_Label
PB3\ (JTDO/TRACESWO).GPIO_Label=SWO
PB3\ (JTDO/TRACESWO).Mode=Trace_Asynchronous_SW
PB3\ (JTDO/TRACESWO).Signal=DEBUG_JTDO-SWO
PB4\ (NJTRST).GPIOParameters=GPIO_Label
PB4\ (NJTRST).GPIO_Label=RESERVED_JTRST
PB4\ (NJTRST).Signal=DEBUG_JTRST
PB5.GPIOParameters=GPIO_Label
PB5.GPIO_Label=SNS_MOSI
PB5.Mode=Full_Duplex_Master
PB5.Signal=SPI1_MOSI
PB6.GPIOParameters=GPIO_Label
PB6.GPIO_Label=SAM-M8Q_SCL
PB6.Mode=I2C
PB6.Signal=I2C1_SCL
PB7.GPIOParameters=GPIO_Label
PB7.GPIO_Label=SAM-M8Q_EXTINT
PB7.Signal=GPIO_Input
PB9.GPIOParameters=GPIO_Label
PB9.GPIO_Label=SAM-MAQ-SDA
PB9.Mode=I2C
PB9.Signal=I2C1_SDA
PC0.GPIOParameters=GPIO_Label
PC0.GPIO_Label=sense_a
PC0.Mode=IN1
PC0.Signal=ADC4_IN1
PC1.GPIOParameters=GPIO_Label
PC1.GPIO_Label=sense_b
PC1.Mode=IN2
PC1.Signal=ADC4_IN2
PC11.GPIOParameters=GPIO_Label
PC11.GPIO_Label=TELEM_MISO
PC11.Mode=Full_Duplex_Master
PC11.Signal=SPI3_MISO
PC12.GPIOParameters=GPIO_Label
PC12.GPIO_Label=TELEM_MOSI
PC12.Mode=Full_Duplex_Master
PC12.Signal=SPI3_MOSI
PC2.GPIOParameters=GPIO_Label
PC2.GPIO_Label=sense_c
PC2.Mode=IN3
PC2.Signal=ADC4_IN3
PC3.GPIOParameters=GPIO_Label
PC3.GPIO_Label=sense_d
PC3.Mode=IN4
PC3.Signal=ADC4_IN4
PC6.GPIOParameters=GPIO_Label
PC6.GPIO_Label=RESERVED_TIM8_CH1_PWM
PC6.Signal=S_TIM8_CH1
PD0.GPIOParameters=GPIO_Label
PD0.GPIO_Label=FMC_D2
PD0.Signal=FMC_D2_DA2
PD1.GPIOParameters=GPIO_Label
PD1.GPIO_Label=FMC_D3
PD1.Signal=FMC_D3_DA3
PD11.GPIOParameters=GPIO_Label
PD11.GPIO_Label=FMC_CLE
PD11.Signal=FMC_A16_CLE
PD12.GPIOParameters=GPIO_Label
PD12.GPIO_Label=FMC_ALE
PD12.Signal=FMC_A17_ALE
PD14.GPIOParameters=GPIO_Label
PD14.GPIO_Label=FMC_D0
PD14.Signal=FMC_D0_DA0
PD15.GPIOParameters=GPIO_Label
PD15.GPIO_Label=FMC_D1
PD15.Signal=FMC_D1_DA1
PD4.GPIOParameters=GPIO_Label
PD4.GPIO_Label=FMC_RE
PD4.Signal=FMC_NOE
PD5.GPIOParameters=GPIO_Label
PD5.GPIO_Label=FMC_WE
PD5.Signal=FMC_NWE
PD6.GPIOParameters=GPIO_Label
PD6.GPIO_Label=FMC_NWAIT
PD6.Signal=FMC_NWAIT
PD7.GPIOParameters=GPIO_Label
PD7.GPIO_Label=FMC_CE
PD7.Mode=NandChipSelect3_1
PD7.Signal=FMC_NCE
PE10.GPIOParameters=GPIO_Label
PE10.GPIO_Label=FMC_D7
PE10.Signal=FMC_D7_DA7
PE11.GPIOParameters=GPIO_Label
PE11.GPIO_Label=TELEM_GPIO_5
PE11.Signal=GPIO_Input
PE12.GPIOParameters=GPIO_Label
PE12.GPIO_Label=TELEM_GPIO_4
PE12.Signal=GPIO_Input
PE13.GPIOParameters=GPIO_Label
PE13.GPIO_Label=TELEM_GPIO_3
PE13.Signal=GPIO_Input
PE14.GPIOParameters=GPIO_Label
PE14.GPIO_Label=TELEM_GPIO_2
PE14.Signal=GPIO_Input
PE15.GPIOParameters=GPIO_Label
PE15.GPIO_Label=TELEM_GPIO_1
PE15.Signal=GPIO_Output
PE2.GPIOParameters=GPIO_Label
PE2.GPIO_Label=LED_RED
PE2.Signal=GPIO_Output
PE3.GPIOParameters=GPIO_Label
PE3.GPIO_Label=LED_ORANGELED_ORANGE
PE3.Signal=GPIO_Output
PE4.GPIOParameters=GPIO_Label
PE4.GPIO_Label=BUZZER_PWM
PE4.Signal=S_TIM3_CH2
PE5.GPIOParameters=GPIO_Label
PE5.GPIO_Label=LED_GREEN
PE5.Signal=GPIO_Output
PE6.GPIOParameters=GPIO_Label
PE6.GPIO_Label=LED_BLUE
PE6.Signal=GPIO_Output
PE7.GPIOParameters=GPIO_Label
PE7.GPIO_Label=FMC_D4
PE7.Signal=FMC_D4_DA4
PE8.GPIOParameters=GPIO_Label
PE8.GPIO_Label=FMC_D5
PE8.Signal=FMC_D5_DA5
PE9.GPIOParameters=GPIO_Label
PE9.GPIO_Label=FMC_D6
PE9.Signal=FMC_D6_DA6
PF0.GPIOParameters=GPIO_Label
PF0.GPIO_Label=LSM9DS1_CS_M
PF0.Signal=GPIO_Input
PF1.GPIOParameters=GPIO_Label
PF1.GPIO_Label=MS5611_CS
PF1.Signal=GPIO_Input
PF11.GPIOParameters=GPIO_Label
PF11.GPIO_Label=LSM9DS1_INT1_M
PF11.Signal=GPIO_Input
PF12.GPIOParameters=GPIO_Label
PF12.GPIO_Label=H3LIS331DL_INT1
PF12.Signal=GPIO_Input
PF13.GPIOParameters=GPIO_Label
PF13.GPIO_Label=H3LIS331DL_INT2
PF13.Signal=GPIO_Input
PF14.GPIOParameters=GPIO_Label
PF14.GPIO_Label=sense_e
PF14.Mode=IN5
PF14.Signal=ADC4_IN5
PF15.GPIOParameters=GPIO_Label
PF15.GPIO_Label=sense_f
PF15.Mode=IN6
PF15.Signal=ADC4_IN6
PF2.GPIOParameters=GPIO_Label
PF2.GPIO_Label=H3LIS331DL_CS
PF2.Signal=GPIO_Input
PF3.GPIOParameters=GPIO_Label
PF3.GPIO_Label=LSM9DS1_CS_A/G
PF3.Signal=GPIO_Input
PF4.GPIOParameters=GPIO_Label
PF4.GPIO_Label=LSM9DS1_INT1_A/G
PF4.Signal=GPIO_Input
PF5.GPIOParameters=GPIO_Label
PF5.GPIO_Label=LSM9DS1_INT2_A/G
PF5.Signal=GPIO_Input
PG0.GPIOParameters=GPIO_Label
PG0.GPIO_Label=sense_vFlight
PG0.Mode=IN7
PG0.Signal=ADC4_IN7
PG1.GPIOParameters=GPIO_Label
PG1.GPIO_Label=sense_vPyro
PG1.Mode=IN8
PG1.Signal=ADC4_IN8
PG10.GPIOParameters=GPIO_Label
PG10.GPIO_Label=fire_a
PG10.Signal=GPIO_Output
PG11.GPIOParameters=GPIO_Label
PG11.GPIO_Label=fire_b
PG11.Signal=GPIO_Output
PG12.GPIOParameters=GPIO_Label
PG12.GPIO_Label=fire_c
PG12.Signal=GPIO_Output
PG13.GPIOParameters=GPIO_Label
PG13.GPIO_Label=fire_d
PG13.Signal=GPIO_Output
PG14.GPIOParameters=GPIO_Label
PG14.GPIO_Label=fire_e
PG14.Signal=GPIO_Output
PG15.GPIOParameters=GPIO_Label
PG15.GPIO_Label=fire_f
PG15.Signal=GPIO_Output
PG3.GPIOParameters=GPIO_Label
PG3.GPIO_Label=SNS_MISO
PG3.Mode=Full_Duplex_Master
PG3.Signal=SPI1_MISO
PG6.GPIOParameters=GPIO_Label
PG6.GPIO_Label=TELEM_INT
PG6.Signal=GPIO_Input
PG7.GPIOParameters=GPIO_Label
PG7.GPIO_Label=TELEM_CS
PG7.Signal=GPIO_Input
PG8.GPIOParameters=GPIO_Label
PG8.GPIO_Label=TELEM_RST
PG8.Signal=GPIO_Input
PG9.GPIOParameters=GPIO_Label
PG9.GPIO_Label=TELEM_SCK
PG9.Mode=Full_Duplex_Master
PG9.Signal=SPI3_SCK
PH0-OSC_IN\ (PH0).GPIOParameters=GPIO_Label
PH0-OSC_IN\ (PH0).GPIO_Label=HSE_CLK
PH0-OSC_IN\ (PH0).Mode=HSE-External-Clock-Source
PH0-OSC_IN\ (PH0).Signal=RCC_OSC_IN
RCC.HSE_VALUE=32000000
RCC.SYSCLKFreq_VALUE=32000000
RCC.SYSCLKSource=RCC_SYSCLKSOURCE_HSE
board=custom
